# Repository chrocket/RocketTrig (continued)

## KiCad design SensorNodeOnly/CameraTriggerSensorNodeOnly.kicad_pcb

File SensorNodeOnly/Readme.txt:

Sensor Node only board

Supports a variety of sensors

Used with jlcpcb pc board fab

This is not stand-alone;  must be used in concert with at least on RocketTrig Node.

Edit Camera_reomote_txrx_sensorNodeOnly.ino
- Select one sensor type only (Sensor_x) and re-compile
- Set behvior of overrideAlwaysArmed
      True - a sensor hit will always trigger camear
      False - a sensor hit will only trigger camera if "armed" is true (use this for sensors with lots of false positives, but you must arm before you are ready to take a picture)

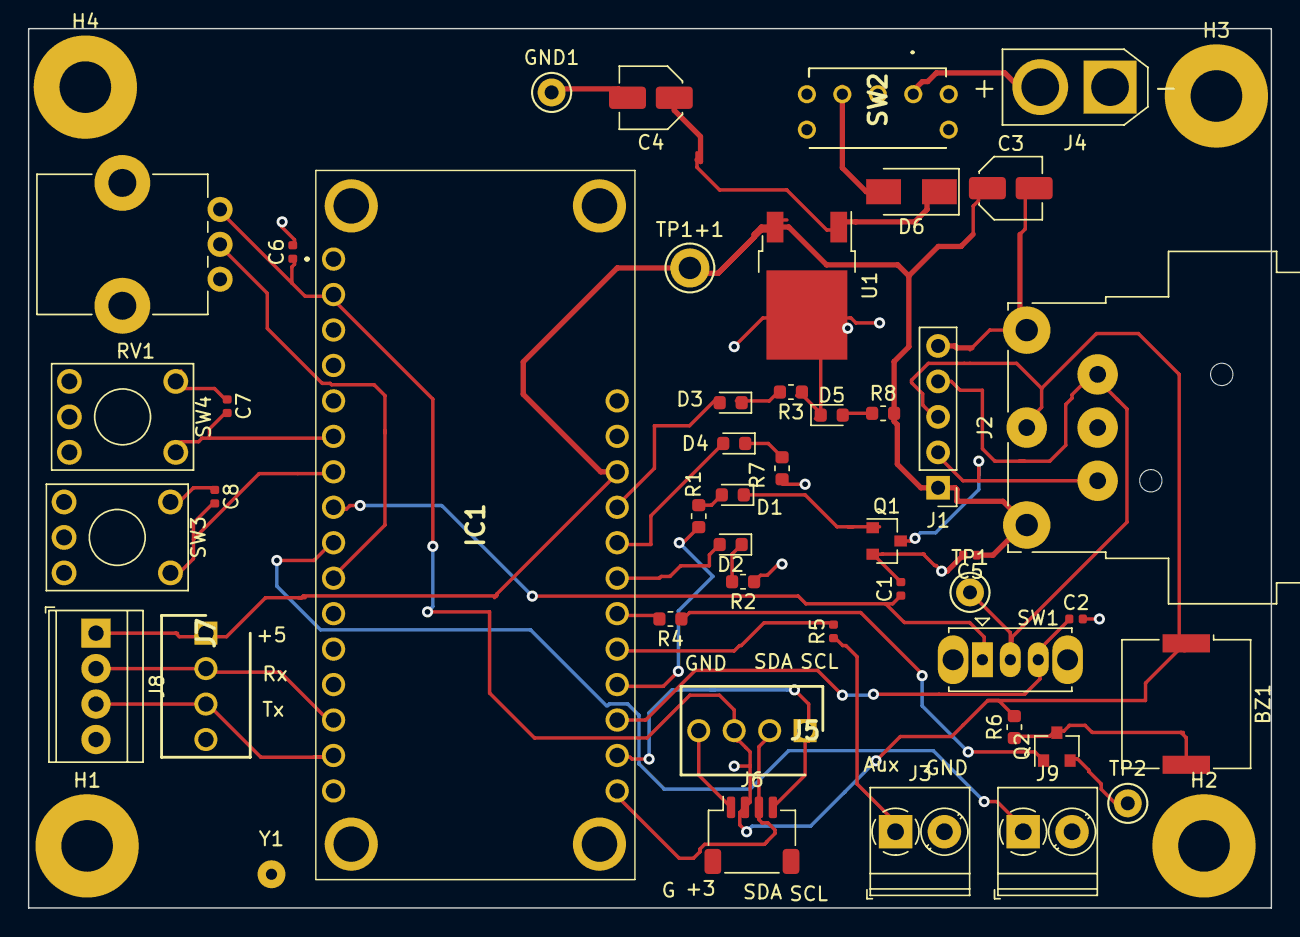
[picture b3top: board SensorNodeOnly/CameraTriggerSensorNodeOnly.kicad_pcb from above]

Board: 2 copper layers, 89.0 x 63.0 mm, 50 parts (0 on the bottom side), 33 nets.

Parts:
BZ1: Buzzer; Buzzer_Murata_PKMCS0909E4000-R1
C1, C2, C5, C6, C7, C8: 0.01 μF; C_0402_1005Metric
C3: 1uf; C_Elec_4x5.4
C4: 25uf; C_Elec_4x5.4
D1: Arm; LED_0603_1608Metric
D2: Trig2; LED_0603_1608Metric
D3: Trig1; LED_0603_1608Metric
D4: Shutter; LED_0603_1608Metric
D5: PWR; LED_0603_1608Metric
D6: SR560-T; D_SMA
GND1: TestPoint; TestPoint_Keystone_5000-5004_Miniature
H1, H2, H3, H4: MountingHole_3.7mm_Pad
IC1: 3178
J1: PinHeader_1x05_P2.54mm_Vertical
J2: XLR5 Male; Jack_XLR_Neutrik_NC5MBH_Horizontal
J3: Aux out; TerminalBlock_Phoenix_PT-1,5-2-3.5-H_1x02_P3.50mm_Horizontal
J4: AMASS_XT30U-F_1x02_P5.0mm_Vertical
J5: HDRV4W64P0X254_1X4_1016X635X1067P
J6: I2C; JST_SH_SM04B-SRSS-TB_1x04-1MP_P1.00mm_Horizontal
J7: Conn_01x04_Male; HDRV4W64P0X254_1X4_1016X635X1067P
J8: Serial; TerminalBlock_TE_282834-4_1x04_P2.54mm_Horizontal
J9: Analog in; TerminalBlock_Phoenix_PT-1,5-2-3.5-H_1x02_P3.50mm_Horizontal
Q1: MMBT3904; SOT-23
Q2: 2SC1815; SOT-23
R1, R2, R3, R4, R6, R7, R8: 1K; R_0603_1608Metric
R5: 5K; R_0402_1005Metric
RV1: 1K; Potentiometer_Alps_RK09K_Single_Vertical
SW1: SW_Slide_1P2T_CK_OS102011MS2Q
SW2: AS11CB
SW3: SW_Poll; KSA_Tactile_SPST
SW4: SW_Arm; KSA_Tactile_SPST
TP1: Sensor; TestPoint_Keystone_5000-5004_Miniature
TP1+1: +5V; TestPoint_Keystone_5010-5014_Multipurpose
TP2: Gnd; TestPoint_Keystone_5000-5004_Miniature
U1: LM7805_TO220; TO-252-2
Y1: SolderWirePad_1x01_Drill0.8mm

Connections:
+3V3: BZ1.1, C6.1, IC1.27, J1.3, J2.3, J5.3, J6.2, R6.2, RV1.1
+5V: C3.1, C5.1, IC1.3, J1.1, J2.1, J7.1, J8.1, R8.2, TP1+1.1, U1.3
+7.5V: J4.2, SW2.1
/Sheet621ECC97/13: D3.2, IC1.4
ANALOG_IN: IC1.20, J9.1
ArmIn: C7.2, IC1.23, SW4.2
ArmInd: IC1.9, R1.2
AuxIn: C1.1, IC1.21, SW1.1
AuxOut: IC1.8, R5.2
Buzzer: IC1.7, R4.2
GND: C1.2, C2.2, C3.2, C4.2, C5.2, C6.2, C7.1, C8.1, D5.1, GND1.1, H1.1, H2.1, H3.1, H4.1, IC1.25, J1.5, J2.5, J3.2, J4.1, J5.4, J6.1, J7.4, J8.4, J9.2, Q1.2, Q2.2, R2.1, R3.1, R7.1, RV1.3, SW3.1, SW4.1, TP2.1, U1.2
Laser: J1.2, J2.2, Q1.3
unnamed: BZ1.2, Q2.3, R6.1
unnamed: C4.1, D6.1, U1.1
unnamed: D1.1, Q1.1
unnamed: D1.2, R1.1
unnamed: D2.1, R2.2
unnamed: D2.2, IC1.6
unnamed: D3.1, R3.2
unnamed: D4.1, R7.2
unnamed: D5.2, R8.1
unnamed: D6.2, SW2.3
unnamed: J1.4, J2.4, SW1.2, TP1.1
unnamed: J3.1, R5.1
unnamed: Q2.1, R4.1
Poll: C8.2, IC1.22, SW3.2
Rx_serial: IC1.15, J7.2, J8.2
SCL_qwiic: IC1.11, J5.1, J6.4
SDA_qwiic: IC1.12, J5.2, J6.3
SensorIn: C2.1, IC1.10, SW1.3
Shutter: D4.2, IC1.5
Threshold: IC1.19, RV1.2
Tx_serial: IC1.14, J7.3, J8.3

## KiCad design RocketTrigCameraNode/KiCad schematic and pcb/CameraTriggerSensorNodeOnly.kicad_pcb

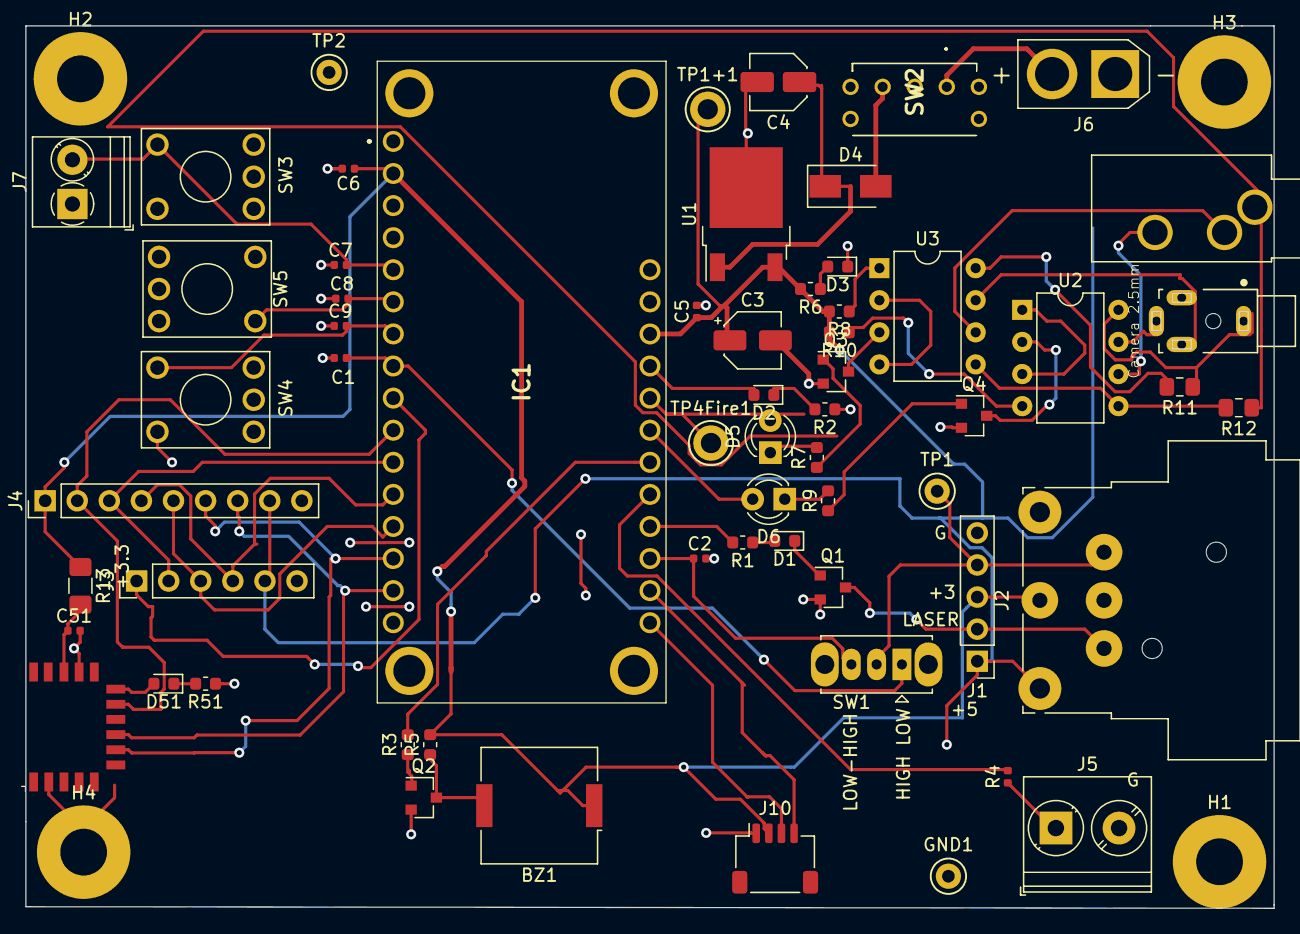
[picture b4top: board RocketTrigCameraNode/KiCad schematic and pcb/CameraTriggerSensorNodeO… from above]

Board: 2 copper layers, 98.8 x 69.9 mm, 65 parts (0 on the bottom side), 56 nets.

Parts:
BZ1: Buzzer; Buzzer_Murata_PKMCS0909E4000-R1
C1, C2, C5, C6, C7, C8, C9: 0.01 μF; C_0402_1005Metric
C3: 1uf; CP_Elec_4x5.4
C4: 25uf; C_Elec_4x5.4
C51: 100n; C_0402_1005Metric
D1: LED Arm; LED_0603_1608Metric
D2: LED Trig; LED_0603_1608Metric
D3: PWR; LED_0603_1608Metric
D4: B330A-13-F; D_SMA
D5: LED Trig; LED_D3.0mm
D6: LED Focus; LED_D3.0mm
D51: BLUE; LED_0603_1608Metric
GND1: TestPoint; TestPoint_Keystone_5000-5004_Miniature
H1, H2, H3, H4: MountingHole_3.7mm_Pad
IC1: 3178
J1: PinHeader_1x05_P2.54mm_Vertical
J2: XLR5 Male; Jack_XLR_Neutrik_NC5MBH_Horizontal
J3: PinHeader_1x06_P2.54mm_Vertical
J4: PinHeader_1x09_P2.54mm_Vertical
J5: Aux out; TerminalBlock_Phoenix_PT-1,5-2-5.0-H_1x02_P5.00mm_Horizontal
J6: AMASS_XT30U-F_1x02_P5.0mm_Vertical
J7: Trig in; TerminalBlock_Phoenix_PT-1,5-2-3.5-H_1x02_P3.50mm_Horizontal
J8: Camera 3.5mm; Jack_3.5mm_CUI_SJ1-3533NG_Horizontal_CircularHoles
J9: Camera 2.5mm; CUI_SJ1-2503A
J10: qwiic; JST_SH_SM04B-SRSS-TB_1x04-1MP_P1.00mm_Horizontal
Q1, Q3, Q4: MMBT3904; SOT-23
Q2: 2SC1815; SOT-23
R1, R2, R3, R5, R6, R7, R9: 1K; R_0603_1608Metric
R4: 5K; R_0402_1005Metric
R8, R10: 51; R_0603_1608Metric
R11, R12: 0; R_0805_2012Metric_Pad1.15x1.40mm_HandSolder
R13: 0; R_1206_3216Metric_Pad1.42x1.75mm_HandSolder
R51: 1k5; R_0603_1608Metric
SW1: SW_Slide_1P2T_CK_OS102011MS2Q
SW2: AS11CB
SW3: SW_trig; KSA_Tactile_SPST
SW4: SW_Poll; KSA_Tactile_SPST
SW5: SW_Arm; KSA_Tactile_SPST
TP1: Sensor; TestPoint_Keystone_5000-5004_Miniature
TP1+1: +5V; TestPoint_Keystone_5010-5014_Multipurpose
TP2: Gnd; TestPoint_Keystone_5000-5004_Miniature
TP4Fire1: Fire; TestPoint_Keystone_5010-5014_Multipurpose
U1: LM7805_TO220; TO-252-2
U2, U3: ILD74; DIP-8_W7.62mm
U5: RN4871; Microchip_RN4871

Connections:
+3V3: BZ1.1, C6.1, IC1.27, J1.3, J2.3, J4.1, J10.2, R5.2, R13.1
+5V: C3.1, C5.1, IC1.3, J1.1, J2.1, J3.5, J4.8, R6.2, R8.2, R10.2, TP1+1.1, U1.3
+7.5V: J6.2, SW2.1
/Sheet621ECC97/13: D2.2, IC1.4
/Sheet621ECC97/A4: IC1.20, J3.1
/Sheet621ECC97/MISO: IC1.16, J3.3, J4.5
/Sheet621ECC97/MOSI: IC1.17, J3.4, J4.4
/Sheet621ECC97/SCK: IC1.18, J3.2, J4.3
ArmIn: C8.2, IC1.23, SW5.2
ArmInd: IC1.9, R1.2
AuxIn: C1.1, IC1.21, SW1.1
AuxOut: IC1.8, R4.2
BLE_reset: IC1.19, J4.2, U5.10
Buzzer: IC1.7, R3.2
Focus: D6.2, IC1.6
GND: C1.2, C2.2, C3.2, C4.2, C5.2, C6.2, C7.1, C8.1, C9.1, C51.2, D3.1, GND1.1, H1.1, H2.1, H3.1, H4.1, IC1.25, J1.5, J2.5, J3.6, J4.9, J5.2, J6.1, J7.1, J10.1, Q1.2, Q2.2, Q3.2, Q4.2, R2.1, R51.1, SW3.1, SW4.1, SW5.1, TP2.1, U1.2, U5.2, U5.13
LED_TXRX: D51.2, U5.11
Laser: J1.2, J2.2, Q1.3
unnamed: BZ1.2, Q2.3, R5.1
unnamed: C4.1, D4.1, U1.1
unnamed: C51.1, R13.2, U5.14
unnamed: D1.1, Q1.1
unnamed: D1.2, R1.1
unnamed: D2.1, R2.2
unnamed: D3.2, R6.1
unnamed: D4.2, SW2.3
unnamed: D5.1, R7.2
unnamed: D6.1, R9.2
unnamed: D51.1, R51.2
unnamed: J1.4, J2.4, SW1.2, TP1.1
unnamed: J5.1, R4.1
unnamed: J8.R, U2.6
unnamed: J8.S, R12.1
unnamed: J8.T, U3.6
unnamed: J9.R, U2.7
unnamed: J9.S, R11.1, U2.8
unnamed: J9.T, U3.7
unnamed: Q2.1, R3.1
unnamed: Q3.1, R7.1
unnamed: Q3.3, U3.3
unnamed: Q4.1, R9.1
unnamed: Q4.3, U2.2
unnamed: R8.1, U3.1
unnamed: R10.1, U2.4
unnamed: R11.2, U3.8
unnamed: R12.2, U2.5, U3.5
unnamed: U2.1, U2.3
unnamed: U3.2, U3.4
PbTrigIn: C7.2, IC1.24, J7.2, SW3.2
Poll: C9.2, IC1.22, SW4.2
SCL_qwiic: IC1.11, J10.4
SDA_qwiic: IC1.12, J10.3
SensorIn: C2.1, IC1.10, SW1.3
Shutter: D5.2, IC1.5, TP4Fire1.1
UART1_RX: IC1.14, J4.7, U5.8
UART1_TX: IC1.15, J4.6, U5.7

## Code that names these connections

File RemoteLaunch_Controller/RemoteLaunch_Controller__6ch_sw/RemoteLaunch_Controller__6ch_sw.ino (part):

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// pin assignments
const unsigned int BUZZER_OUT_PIN = 10;  // Pin to audible indicator
//const unsigned int CAMERA_TRIGGER_OUT_PIN = 12;  // Pin for shtter opto-isoloatr
//const unsigned int CAMERA_FOCUS_OUT_PIN = 11;    // Pin for focus opto-isolator
const unsigned int ARM_OUT_PIN = 0;   //MCP23017Pin::GPA0;
const unsigned int FIRE_CH1_PIN = 1;  //MCP23017Pin::GPA1;
const unsigned int FIRE_CH2_PIN = 2;  //MCP23017Pin::GPA2;
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


const unsigned int FIRE_INDICATOR_OUT_PIN = 16;  // D_2
const unsigned int ARM_INDICATOR_OUT_PIN = 17;   // OUT_2  // check


// Radio module stuff
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
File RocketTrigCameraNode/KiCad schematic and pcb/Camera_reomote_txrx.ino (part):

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const unsigned int HIGHLOW_TRIGGER_IN_PIN=17;  // If armed, High to low transition will trigger
const unsigned int PUSH_IN_PIN=14; // Push button trigger override ("arm" does not have to be set)
const unsigned int ARM_IN_PIN=15;  // Push button to arm sensor
const unsigned int POLLREQUEST_IN_PIN=16;  // Push button to send roll call poll request to other nodes
const unsigned int DELAYMS_PIN=18;  // Pot on analog in to set delay 0-200 ms
const unsigned int SPARE_PIN=19;  // Reserved for future use

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// LED_OUT 13
const unsigned int BUZZER_OUT_PIN= 10;            // Pin to audible indicator
const unsigned int CAMERA_TRIGGER_OUT_PIN = 12;   // Pin for shtter opto-isoloatr
const unsigned int CAMERA_FOCUS_OUT_PIN = 11;     // Pin for focus opto-isolator
const unsigned int AUX_OUT_PIN = 9;               // Pin for 2nd trigger output
const unsigned int ARM_INDICATOR_OUT_PIN = 6;     // Indicates sensor is armed, turns laser on

const unsigned int  ON_TIME_MS = 2000 ;          // Camera bulb on time when trigger fires (typical vals 1-3 seconds)      
const unsigned int  SHORT_TIME_MS = 200;
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
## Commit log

2022-07-31 Latest version
2022-07-31 Update README.md
    Added photos plus some notes
2022-08-03 Adding dependencies and build nots
2023-04-02 Setting "focus" to go off simultaneously when there is a shutter trigger
2023-04-02 Adding sensor node pcb files, arduino program, bom, etc.
2023-06-14 Using the CameraTrig board as a remote launcher.
2023-06-16 Schematics
2023-06-16 JLBPCBfab stuff
    - JLBPCBfab stuff
    - Kicad project for CameraTrig Rev 4_1
2023-06-18 Create RemoteLaunch_Controller_SW.ino
    Moving file
2023-06-18 Adding BOM (non JLCPCB parts)
2023-06-18 Moving files
2023-07-02 Adding 4.2 design Unit tests
2023-07-02 Removing Rev 4_1 as Rev 4_2 replaces it
2023-07-02 Removing old version
2023-07-02 Adding graphics
2023-07-03 Update to Kicad 7
2023-07-04 Adding 4ch relay board
2023-07-04 Moving some files around
2023-07-04 Renaming sw files
2023-07-04 Starting to work on RocketTrig_Rev4_2_board_1ch_sw (doesn't work yet)
2023-07-05 Adding UT for mcp23017 i/o on rev4_2 board
2023-07-05 Rev4_2 1 ch board works now
2023-07-08 Adding schematics
2023-07-09 Merge
2023-07-09 Adding Rev4_3
2023-07-10 Adding Rev4_3 rev
2023-07-10 Updating UT that cycles through outputs
2023-07-10 Turning off a debug aspect that requires attaching a serial monitor for the program to run
2023-07-11 Fixing glitch in relay board; Sending REv4_3 to fab
2023-07-21 Printing relay board schematic
2023-11-19 Changing armed time from 10s to 60s; Putting i/o pin for "launch trigger" (default) of cameras, or external sensor
2023-11-24 Adding local/remote; Poll for remote note w/ response to LED
2023-12-21 latest changes
2023-12-22 Working with remote
2023-12-23 Works with state machines for mcp commands; relays on remote still sycle frequently - TODO fix this
2023-12-23 Split prog into Rx and Tx
2023-12-23 Splitting into Rx/Tx.
2023-12-23 Removing old program.
2023-12-24 Works!
2023-12-24 Ongoing
2023-12-24 Changed Rx loop
2023-12-25 Added heartbeats; Buzzer when armed (tx); rx buzzer goes when fired, but TODO needs to be for armed
2023-12-31 Adding panel diagrams and lightburn files
2023-12-31 Redoing layout of remote panel
2024-01-01 Updating hole dims for fuse
2024-01-10 Splitting small into LWHPR and mine.
2024-01-27 Working on adding polling / heartbeat; Seem to have broken launch
2024-01-29 Finally, basically working again.
2024-01-30 Removed mcp line that was immediately turning relays off. Yeah! Works now as before.
2024-01-30 Beep works while armed ... on both Tx and Rx
2024-02-01 Chnge to relay board
2024-07-21 Fixed 1ch 4_3 so that remote sensor will trigger camera in "remote" position
2024-07-21 Making remote/local switch for triggering camera. Local will be launch button, remote will be external lsensor
2024-08-05 Major rework to get remote note to work with camera sensor.
2025-01-12 Update RemoteLaunch_Controller__6ch_sw_RX.ino
    Fixing ch4 so that it stays on for 2 sec ; Manually ported some changes from main
2025-01-13 First fully functional version
